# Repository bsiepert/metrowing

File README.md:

# metrowing
A an adapter to use Adafruit featherwings with Adafruit Metros or Arduino Unos

[BOM on Octopart](https://octopart.com/bom-tool/s72yPqrf)

mkii fixes/updates:
* Adds a SPI header so that we can pick up the SPI/ICSP header on the Metro and route MOSI/MISO/SCK to the appropriate FeatherWing pins. A female ICSP header should be mounted *underneath* the featherwing so that it can plug into the male ICSP header on the Metro. This will allow for use of the LoRa feathers and others that need SPI
* Routes the Metro's +5v to the USB power rails on the feather for Wings that need more juice like the NeoPixel Featherwing
* Adjusts header locations for better clearance
* Fixes pin labels 
* Changes Reset button
* Added 15 pieces of flair

As of 11/15/17 this version is untested

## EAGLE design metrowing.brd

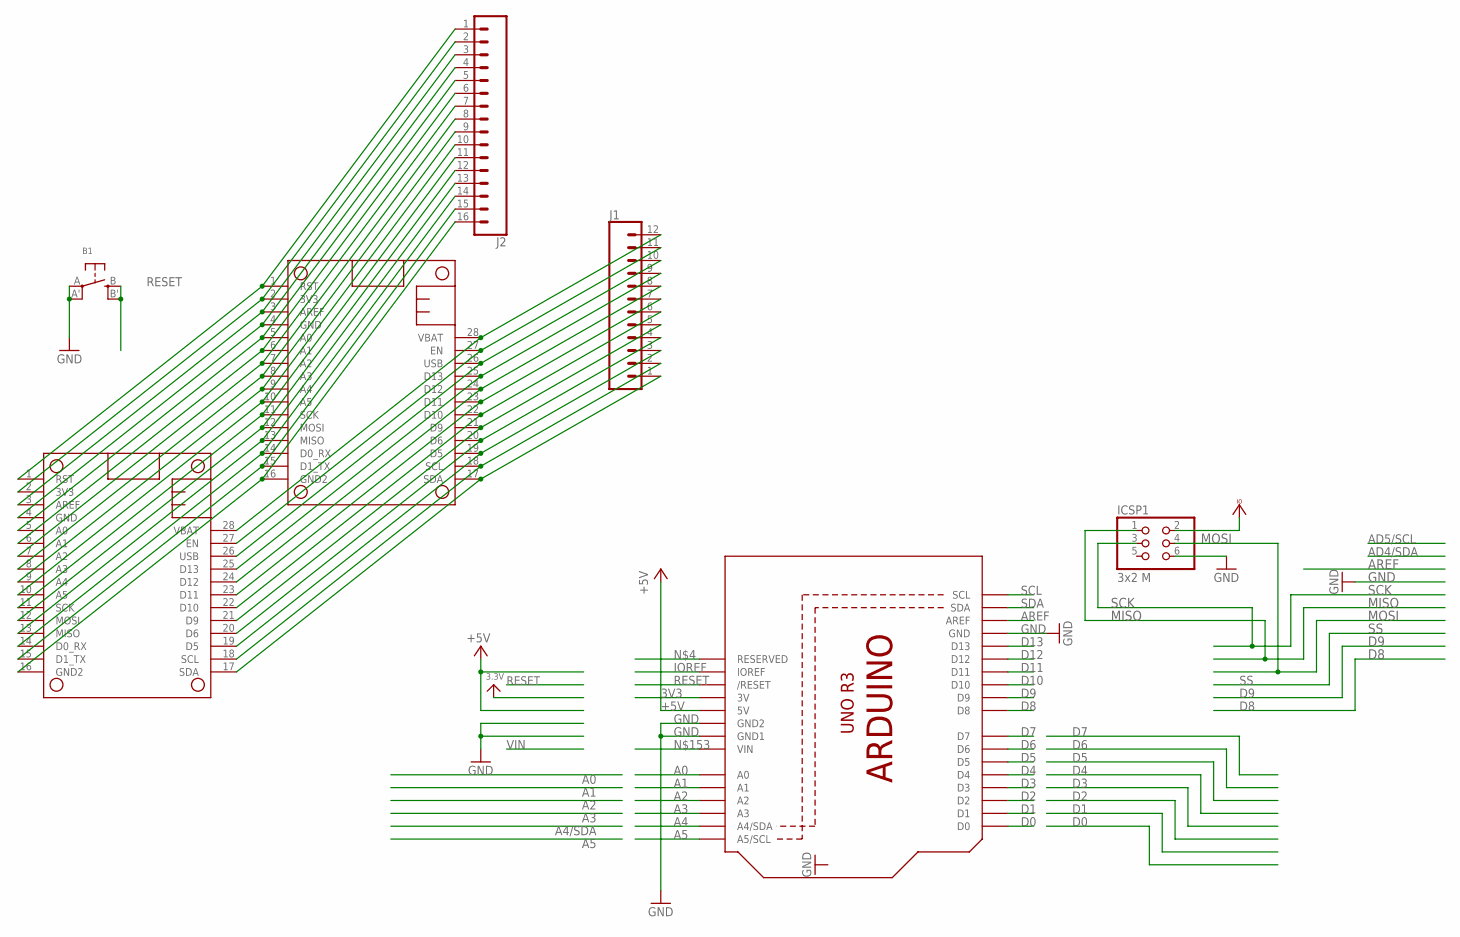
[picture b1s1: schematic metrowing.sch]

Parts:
B1: SWITCH_TACT_SMT; EVQ-Q2
ICSP1: 3x2 M; 2X03_ROUND_70MIL
J1: CONN_12; 1X12
J2: CONN_16; 1X16
MS1, MS2: FEATHERWING_PINS
U1: ARDUINOR3-DIMENSION; ARDUINOR3

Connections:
3V3: J2.2, MS1.2 (3V3), MS2.2 (3V3), U1.3V
+5V: J1.10, MS1.26 (USB), MS2.26 (USB), U1.5V
A0: J2.5, MS1.5 (A0), MS2.5 (A0), U1.A0
A1: J2.6, MS1.6 (A1), MS2.6 (A1), U1.A1
A2: J2.7, MS1.7 (A2), MS2.7 (A2), U1.A2
A3: J2.8, MS1.8 (A3), MS2.8 (A3), U1.A3
A4: J2.9, MS1.9 (A4), MS2.9 (A4), U1.A4 (A4/SDA)
A5: J2.10, MS1.10 (A5), MS2.10 (A5), U1.A5 (A5/SCL)
AREF: J2.3, MS1.3 (AREF), MS2.3 (AREF), U1.AREF
D0: J2.14, MS1.14 (D0_RX), MS2.14 (D0_RX), U1.D0
D1: J2.15, MS1.15 (D1_TX), MS2.15 (D1_TX), U1.D1
D2: U1.D2
D3: U1.D3
D4: U1.D4
D5: J1.3, MS1.19 (D5), MS2.19 (D5), U1.D5
D6: J1.4, MS1.20 (D6), MS2.20 (D6), U1.D6
D7: U1.D7
D8: U1.D8
D9: J1.5, MS1.21 (D9), MS2.21 (D9), U1.D9
D10: J1.6, MS1.22 (D10), MS2.22 (D10), U1.D10
D11: J1.7, MS1.23 (D11), MS2.23 (D11), U1.D11
D12: J1.8, MS1.24 (D12), MS2.24 (D12), U1.D12
D13: J1.9, MS1.25 (D13), MS2.25 (D13), U1.D13
ENABLE: J1.11, MS1.27 (EN), MS2.27 (EN)
GND: B1.A, B1.A' (P1), ICSP1.6, J2.4, J2.16, MS1.4 (GND), MS1.16 (GND2), MS2.4 (GND), MS2.16 (GND2), U1.GND, U1.GND1, U1.GND2
IOREF: U1.IOREF
MISO: ICSP1.1, J2.13, MS1.13 (MISO), MS2.13 (MISO)
MOSI: ICSP1.4, J2.12, MS1.12 (MOSI), MS2.12 (MOSI)
RESET: B1.B (S), B1.B' (S1), J2.1, MS1.1 (RST), MS2.1 (RST), U1.RESET (/RESET)
SCK: ICSP1.3, J2.11, MS1.11 (SCK), MS2.11 (SCK)
SCL: J1.2, MS1.18 (SCL), MS2.18 (SCL), U1.SCL
SDA: J1.1, MS1.17 (SDA), MS2.17 (SDA), U1.SDA
VBAT: J1.12, MS1.28 (VBAT), MS2.28 (VBAT)
VCCIO: ICSP1.2

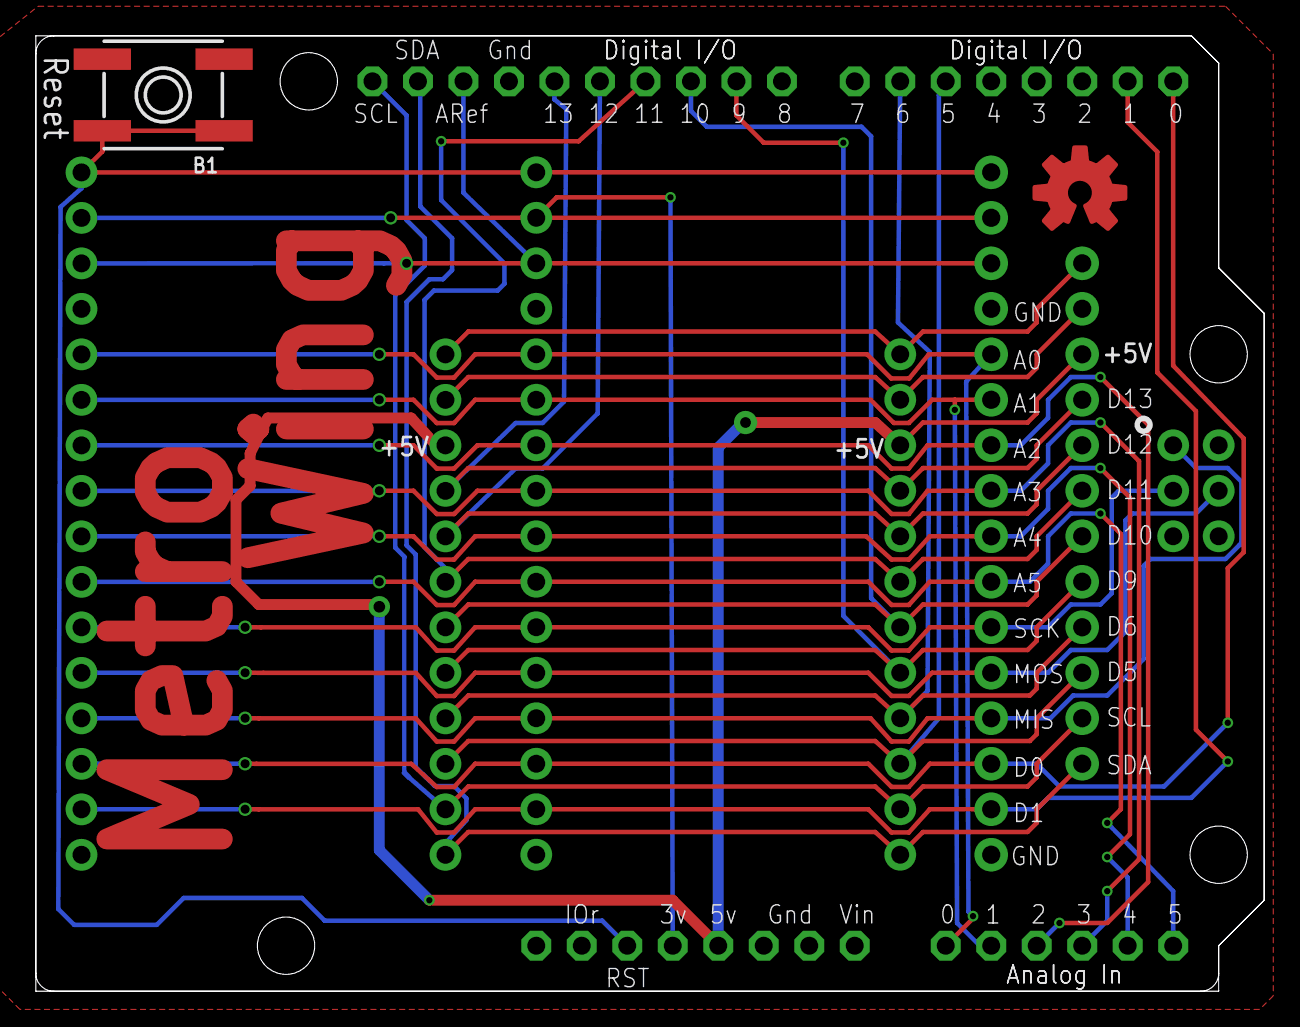
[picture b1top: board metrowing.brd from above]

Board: 2 copper layers, 68.6 x 53.3 mm, 8 parts (0 on the bottom side), 27 nets.

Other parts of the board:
U$1: OSHWLOGO_TOP_0.2

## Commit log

2017-10-20 Initial routed version
2017-10-20 correct (mkii) version
2017-10-20 fixed clearance drc
2017-10-27 Broken SPI Notificaion
2017-11-16 updated and fixed mkii: Now with more SPI

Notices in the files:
parts and their libraries:
SparkFun-Connectors: Licensing: Creative Commons ShareAlike 4.0 International - https://creativecommons.org/licenses/by-sa/4.0
microbuilder: This work is placed in the public domain, and may be freely used for commercial and non-commercial work with the following conditions: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
